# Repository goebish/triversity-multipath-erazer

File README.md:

# DIY Triversity 5.8 Ghz Video Receiver

## Building

Requires Arduino >= 1.6

PDQ_GFX for ST7735 must be installed in the Arduino libraries folder.

## Usage

### Main dialog

Press left or right to change channel, long press enable auto scan

Press up to enter calibration / bargraph dialog

### Calibration procedure

Allow the Triversity receiver to warm up for at least 5-10 minutes before calibrating.

- Start with transmitter switched off
- Press left / right to manually set frequency to the same as your transmitter
- Press up to enter calibration / bargraph dialog
- Set gain potentiometers to their maximum position
- Adjust zero adjust potentiometers until every channel read the same value in the 50-60 range, lower is better, but they must read the same value, ie 51 51 51
- Switch transmitter on
- Adjust gain potentiometer until every channel read 1000
- Press up to exit calibration dialog

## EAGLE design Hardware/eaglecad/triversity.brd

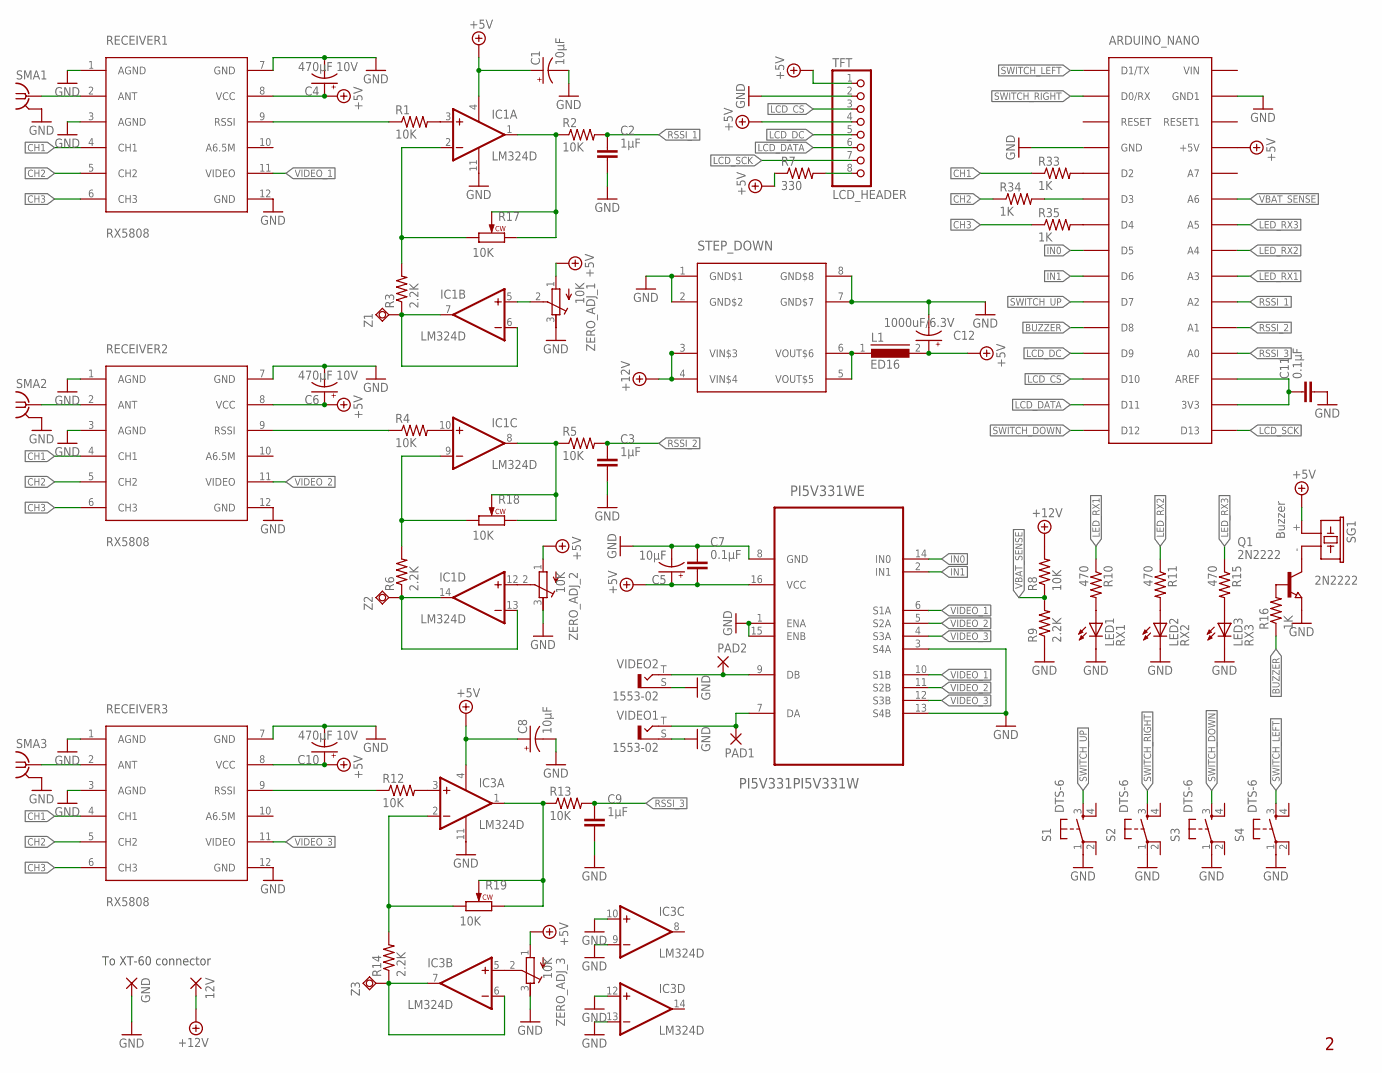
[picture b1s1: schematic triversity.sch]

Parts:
12V: WIREPAD4,16O1,6; 4,16O1,6
ARDUINO_NANO: ARDUINO_NANO; PDIP-32
C1, C5, C8: 10µF; EIA3216-KIT
C2, C3, C9: 1µF; C805
C4, C6, C10: 470µF 10V; EIA7343
C7, C11: 0.1µF; C805
C12: 1000uF/6.3V; E5-10,5
GND: WIREPAD4,16O1,6; 4,16O1,6
IC1, IC3: LM324D; SO14
L1: ED16
LED1: RX1; LED3MM
LED2: RX2; LED3MM
LED3: RX3; LED3MM
PAD1, PAD2: WIREPADSMD1,27-254; SMD1,27-2,54
PI5V331WE: PI5V331PI5V331W; SO16
Q1: 2N2222; SOT23
R1, R2, R4, R5, R8, R12, R13: 10K; M0805
R3, R6, R9, R14: 2.2K; M0805
R7: 330; M0805
R10, R11, R15: 470; M0805
R16, R33, R34, R35: 1K; M0805
R17, R18, R19: 10K; RK09L-SINGLE
RECEIVER1, RECEIVER2, RECEIVER3: RX5808
S1, S2, S3, S4: DTS-6
SG1: Buzzer; F/CM12P
SMA1, SMA2, SMA3: SMA-142-0711-821/826; J502-ND-142-0711-821/826
STEP_DOWN: LM2596_MODULE; LM2596-MODULE
TFT: LCD_HEADER; 1X08-CLEANBIG
VIDEO1, VIDEO2: 1553-02
Z1, Z2, Z3: TP-M; KEY-MINIATURE
ZERO_ADJ_1, ZERO_ADJ_2, ZERO_ADJ_3: 10K; RTRIM3296X

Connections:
3V3_AREF: ARDUINO_NANO.3V3, ARDUINO_NANO.AREF, C11.1
+5V: ARDUINO_NANO.+5V, C1.A (+), C4.A (+), C5.A (+), C6.A (+), C7.2, C8.A (+), C10.A (+), C12.+, IC1.4 (V+), IC3.4 (V+), L1.2, PI5V331WE.16 (VCC), R7.1, RECEIVER1.8 (VCC), RECEIVER2.8 (VCC), RECEIVER3.8 (VCC), SG1.+ (1), TFT.1, TFT.4, ZERO_ADJ_1.1 (E), ZERO_ADJ_2.1 (E), ZERO_ADJ_3.1 (E)
+12V: 12V.1, R8.2, STEP_DOWN.3 (VIN$3), STEP_DOWN.4 (VIN$4)
ANT1: RECEIVER1.2 (ANT), SMA1.1
ANT2: RECEIVER2.2 (ANT), SMA2.1
ANT3: RECEIVER3.2 (ANT), SMA3.1
BUZZER: ARDUINO_NANO.D8, R16.1
CH1: R33.1, RECEIVER1.4 (CH1), RECEIVER2.4 (CH1), RECEIVER3.4 (CH1)
CH2: R34.1, RECEIVER1.5 (CH2), RECEIVER2.5 (CH2), RECEIVER3.5 (CH2)
CH3: R35.1, RECEIVER1.6 (CH3), RECEIVER2.6 (CH3), RECEIVER3.6 (CH3)
GND: ARDUINO_NANO.GND, ARDUINO_NANO.GND1, C1.C (-), C2.2, C3.2, C4.C (-), C5.C (-), C6.C (-), C7.1, C8.C (-), C9.2, C10.C (-), C11.2, C12.-, GND.1, IC1.11 (V-), IC3.9 (-IN), IC3.10 (+IN), IC3.11 (V-), IC3.12 (+IN), IC3.13 (-IN), LED1.K (C), LED2.K (C), LED3.K (C), PI5V331WE.1 (ENA), PI5V331WE.3 (S4A), PI5V331WE.8 (GND), PI5V331WE.13 (S4B), PI5V331WE.15 (ENB), Q1.2 (E), R9.1, RECEIVER1.1 (AGND), RECEIVER1.3 (AGND), RECEIVER1.7 (GND), RECEIVER1.12 (GND), RECEIVER2.1 (AGND), RECEIVER2.3 (AGND), RECEIVER2.7 (GND), RECEIVER2.12 (GND), RECEIVER3.1 (AGND), RECEIVER3.3 (AGND), RECEIVER3.7 (GND), RECEIVER3.12 (GND), S1.1, S2.1, S3.1, S4.1, SMA1.G@1 (GND), SMA1.G@2 (GND), SMA1.G@3 (GND), SMA1.G@4 (GND), SMA2.G@1 (GND), SMA2.G@2 (GND), SMA2.G@3 (GND), SMA2.G@4 (GND), SMA3.G@1 (GND), SMA3.G@2 (GND), SMA3.G@3 (GND), SMA3.G@4 (GND), STEP_DOWN.1 (GND$1), STEP_DOWN.2 (GND$2), STEP_DOWN.7 (GND$7), STEP_DOWN.8 (GND$8), TFT.2, VIDEO1.S, VIDEO2.S, ZERO_ADJ_1.3 (A), ZERO_ADJ_2.3 (A), ZERO_ADJ_3.3 (A)
IN0: ARDUINO_NANO.D5, PI5V331WE.14 (IN0)
IN1: ARDUINO_NANO.D6, PI5V331WE.2 (IN1)
LCD_CS: ARDUINO_NANO.D10, TFT.3
LCD_DATA: ARDUINO_NANO.D11, TFT.6
LCD_DC: ARDUINO_NANO.D9, TFT.5
LCD_SCK: ARDUINO_NANO.D13, TFT.7
LED_RX1: ARDUINO_NANO.A3, R10.1
LED_RX2: ARDUINO_NANO.A4, R11.1
LED_RX3: ARDUINO_NANO.A5, R15.1
unnamed: IC1.3 (+IN), R1.2
unnamed: IC3.3 (+IN), R12.2
unnamed: IC1.1 (OUT), R2.1, R17.2 (W), R17.3 (CW)
unnamed: R7.2, TFT.8
unnamed: IC1.6 (-IN), IC1.7 (OUT), R3.1, Z1.P$1
unnamed: IC1.2 (-IN), R3.2, R17.1 (CCW)
unnamed: IC1.10 (+IN), R4.2
unnamed: IC1.5 (+IN), ZERO_ADJ_1.2 (S)
unnamed: IC1.8 (OUT), R5.1, R18.2 (W), R18.3 (CW)
unnamed: IC1.13 (-IN), IC1.14 (OUT), R6.1, Z2.P$1
unnamed: IC1.9 (-IN), R6.2, R18.1 (CCW)
unnamed: IC1.12 (+IN), ZERO_ADJ_2.2 (S)
unnamed: Q1.3 (C), SG1.- (2)
unnamed: IC3.1 (OUT), R13.1, R19.2 (W), R19.3 (CW)
unnamed: IC3.6 (-IN), IC3.7 (OUT), R14.1, Z3.P$1
unnamed: IC3.2 (-IN), R14.2, R19.1 (CCW)
unnamed: IC3.5 (+IN), ZERO_ADJ_3.2 (S)
unnamed: LED1.A, R10.2
unnamed: Q1.1 (B), R16.2
unnamed: L1.1, STEP_DOWN.5 (VOUT$5), STEP_DOWN.6 (VOUT$6)
unnamed: LED2.A, R11.2
unnamed: LED3.A, R15.2
unnamed: ARDUINO_NANO.D2, R33.2
unnamed: ARDUINO_NANO.D3, R34.2
unnamed: ARDUINO_NANO.D4, R35.2
RAW_RSSI1: R1.1, RECEIVER1.9 (RSSI)
RAW_RSSI2: R4.1, RECEIVER2.9 (RSSI)
RAW_RSSI3: R12.1, RECEIVER3.9 (RSSI)
RSSI_1: ARDUINO_NANO.A2, C2.1, R2.2
RSSI_2: ARDUINO_NANO.A1, C3.1, R5.2
RSSI_3: ARDUINO_NANO.A0, C9.1, R13.2
SWITCH_DOWN: ARDUINO_NANO.D12, S3.3
SWITCH_LEFT: ARDUINO_NANO.D1/TX, S4.3
SWITCH_RIGHT: ARDUINO_NANO.D0/RX, S2.3
SWITCH_UP: ARDUINO_NANO.D7, S1.3
VBAT_SENSE: ARDUINO_NANO.A6, R8.1, R9.2
VIDEO_1: PI5V331WE.6 (S1A), PI5V331WE.10 (S1B), RECEIVER1.11 (VIDEO)
VIDEO_2: PI5V331WE.5 (S2A), PI5V331WE.11 (S2B), RECEIVER2.11 (VIDEO)
VIDEO_3: PI5V331WE.4 (S3A), PI5V331WE.12 (S3B), RECEIVER3.11 (VIDEO)
VIDEO_OUT1: PAD1.1, PI5V331WE.7 (DA), VIDEO1.T
VIDEO_OUT2: PAD2.1, PI5V331WE.9 (DB), VIDEO2.T

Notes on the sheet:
To XT-60 connector
2N2222

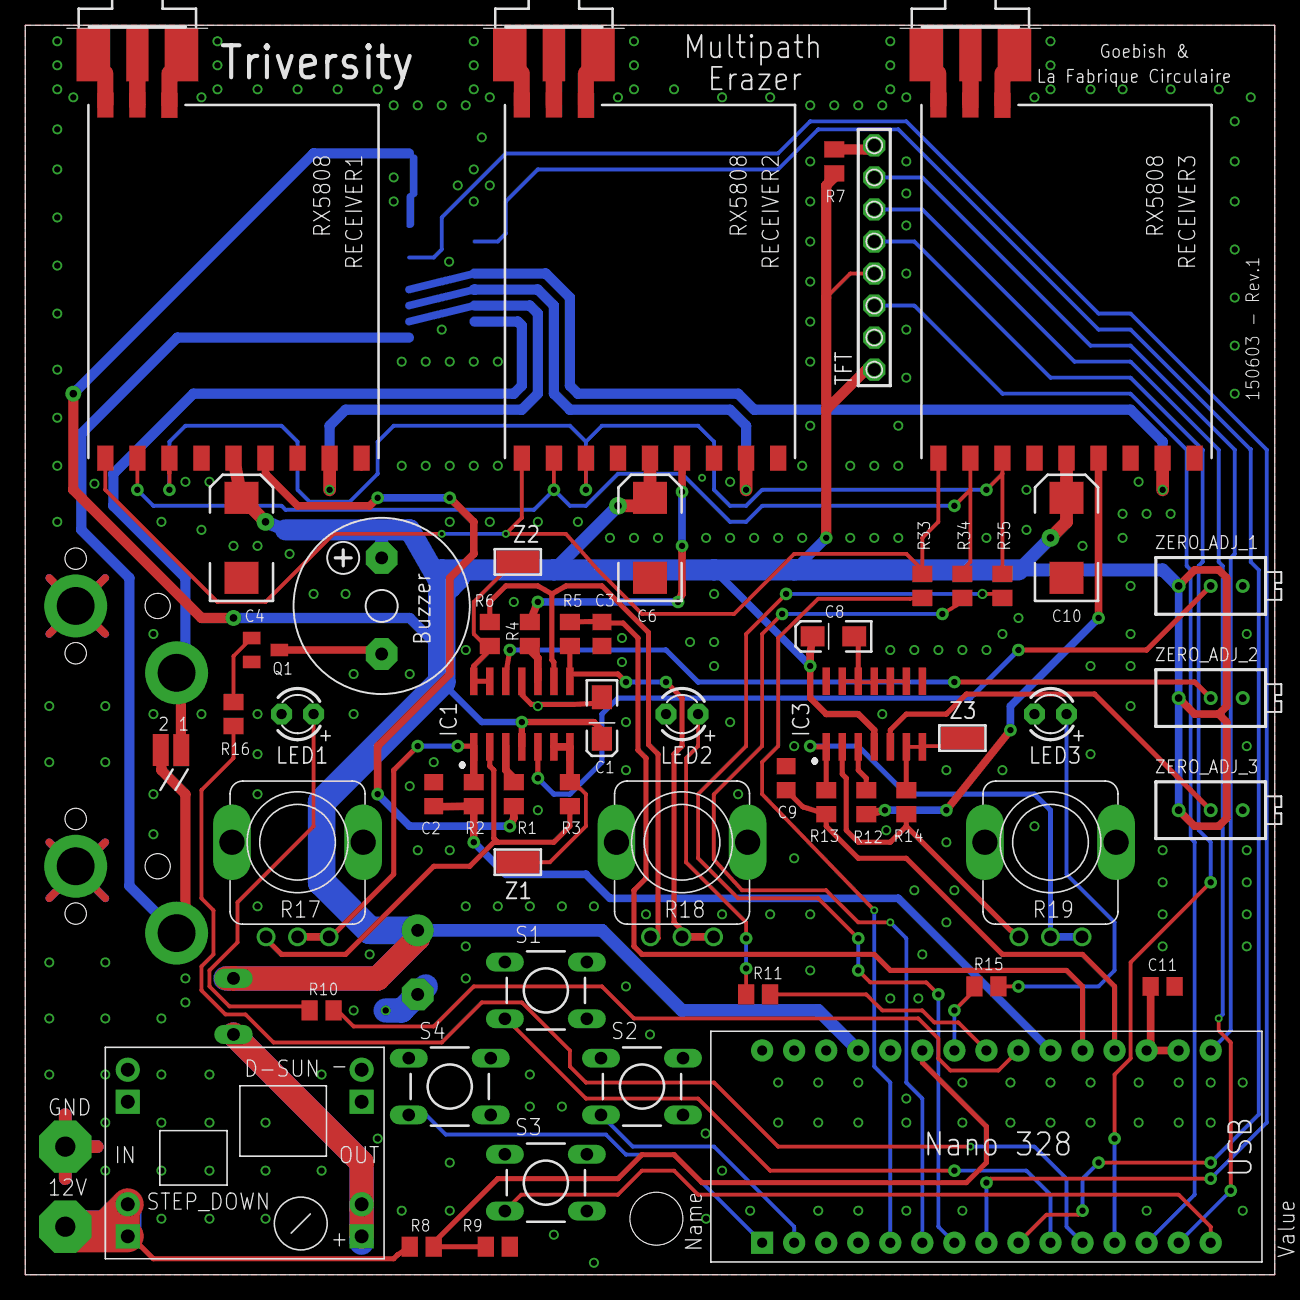
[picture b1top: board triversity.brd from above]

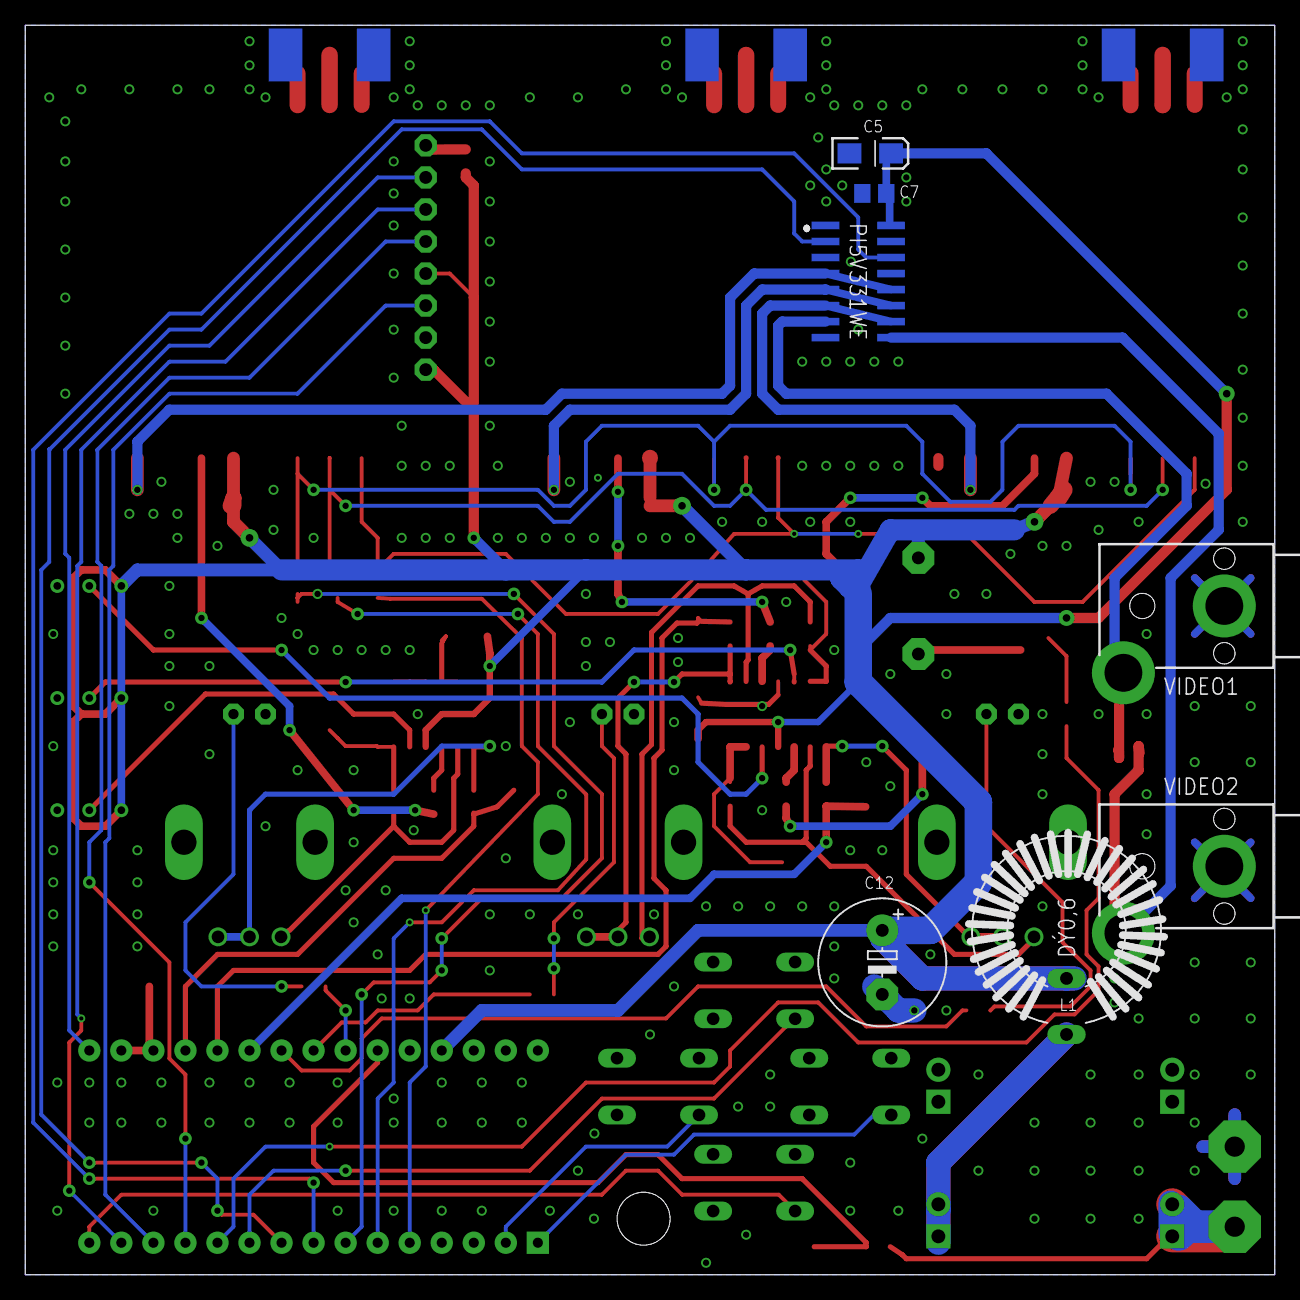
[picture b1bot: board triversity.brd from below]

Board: 2 copper layers, 99.1 x 99.1 mm, 69 parts (7 on the bottom side), 61 nets.

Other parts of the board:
U$1: ST7735-SPI

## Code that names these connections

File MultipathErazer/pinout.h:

// global pinout

// TFT LCD
#define TFT_CS (uint8_t)    10
#define TFT_RST (uint8_t)   A7   // connected to +3.3
#define TFT_DC (uint8_t)    9
#define TFT_SCLK (uint8_t)  13
#define TFT_DATA (uint8_t)  11

// buttons
#define BTN_UP_PIN  (uint8_t)   7
#define BTN_RIGHT_PIN (uint8_t) 0
#define BTN_DOWN_PIN (uint8_t)  12
#define BTN_LEFT_PIN (uint8_t)  1

#define BTN_UP      (!(PIND & 0b10000000))
#define BTN_RIGHT   (!(PIND & 0b00000001))
#define BTN_DOWN    (!(PINB & 0b00010000))
#define BTN_LEFT    (!(PIND & 0b00000010))
#define BTN_ANY     (BTN_UP|BTN_RIGHT|BTN_LEFT|BTN_DOWN)


// SPI vRX
#define VRX_DATA (uint8_t)  2 // PD2 - CH1 
#define VRX_EN (uint8_t)    3 // PD3 - CH2
#define VRX_CLK (uint8_t)   4 // PD4 - CH3

// RSSI vRX
#define RSSI_1 (uint8_t)    A2
#define RSSI_2 (uint8_t)    A1
#define RSSI_3 (uint8_t)    A0 

// LEDs
#define LED_VRX_1 (uint8_t) A3 
#define LED_VRX_2 (uint8_t) A4 
#define LED_VRX_3 (uint8_t) A5 

// analog multiplexer control
#define PI5V311_IN0 (uint8_t) 5 // PD5
#define PI5V311_IN1 (uint8_t) 6 // PD6

// misc
#define BUZZER (uint8_t)    8   // PB0
#define BUZZ_OFF PORTB &= ~0b00000001
#define BUZZ_ON  PORTB |=  0b00000001

#define VBAT (uint8_t)      A6

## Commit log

2015-07-04 Add auto channel scanning
2015-07-04 Fix auto scan
2015-07-04 Auto scan on long press
2015-07-04 Show led for active vRX + all other vRX(s) with same RSSI
2015-07-04 Rearrange splash screen
2015-07-04 Allow more time for RSSI stabilization
2015-07-05 Add TFT cursor location helper
2015-07-05 Fix beep when auto scan is canceled
2015-07-05 Draw larger rectangle around current channel #
2015-07-05 Fix start of auto scan when already on good channel
2015-07-05 Add led animation during auto scan
2015-07-05 Smoother / faster auto scan
2015-07-05 Better LEDs animations
2015-07-05 Fix calibration bargraphs
2015-07-05 README.md edited online with Bitbucket
2015-07-05 Fix RSSI values display in calibration dialog
2015-07-06 Add double beep on auto find
2015-07-07 Triple beep on auto find
2015-07-07 Fix bargraphs
2015-07-07 Add beep when entering a new band in auto scan
2015-07-07 Add vRX numbers in bar graphs dialog
2015-07-07 Add dialog titles
2015-07-07 Add 3 beeps at end of splash screen
2015-07-07 Reorganize main dialog labels
2015-07-07 Reorganize RSSI levels dialog
2015-07-07 Change dialog title during auto scan
2015-07-07 Fix main dialog title refreshed on each pass
2015-07-07 Re-enable diversity in main dialog
2015-07-07 Add main menu
2015-07-07 Faster menu navigation
2015-07-08 Rename main dialog title
2015-07-08 Allow channel change in bar graph (RSSI) dialog
2015-07-08 Allow auto scan in bar graph dialog
2015-07-08 Animate bar graph during auto search
2015-07-09 Add empty placeholders for band scanner and settings menu
2015-07-09 Add voltage alarm beep, fixed at 10.9 Volt for now
2015-07-11 Add basic band scanner
2015-07-11 Band scanner shows best channel
2015-07-11 Show best channel in real time
2015-07-12 Add bitmap logo
2015-07-12 Optimize RLE decoder
2015-07-13 Fix scanner bars height
2015-07-13 Add scale bars for RSSI monitor
2015-07-13 Smoother refresh of RSSI value labels
2015-07-13 Avoid false positive during auto search
2015-07-13 Start with white screen for better splash screen display
2015-07-13 Wait one complete pass before displaying best channel
2015-07-13 Add best channel selection in band scanner mode
2015-07-13 Set channel only if frequency has changed
2015-07-13 Store strings in program memory, free 150 bytes of RAM
2015-07-13 Update left and right arrow characters
2015-07-14 Fix beep when searching in backward direction
2015-07-14 Smoother battery voltage refresh
2015-07-14 Add more strings to display.h to ease future translations
2015-11-02 Add settings menu, beep on switch, battery alarm setting, minimum switch period setting
2015-11-02 Clean up
2019-05-19 Add hardware
2019-05-19 Add pictures
2019-05-19 Add pcb renderings
2019-05-19 Add casing
2019-05-20 Add png schematics

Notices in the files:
parts and their libraries:
SparkFun-Passives: Licensing: CC v3.0 Share-Alike You are welcome to use this library for commercial purposes.
